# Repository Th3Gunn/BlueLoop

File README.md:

BluePill devboard based project - ultra compact guitar loop switcher controlled entirely through MIDI TRS (something like Morningstar ML5R).
Includes 0.96" I2C LCD module, few buttons (only for programming), USB-C for flashing and USB MIDI. 
5 relay controlled loops (relays controlled with 74HC595 bit shift register), and discrete MOSFET input and  output mute circuit.

Future plans are to make completely custom board (without BluePill module) and to create Windows application for preset programming.

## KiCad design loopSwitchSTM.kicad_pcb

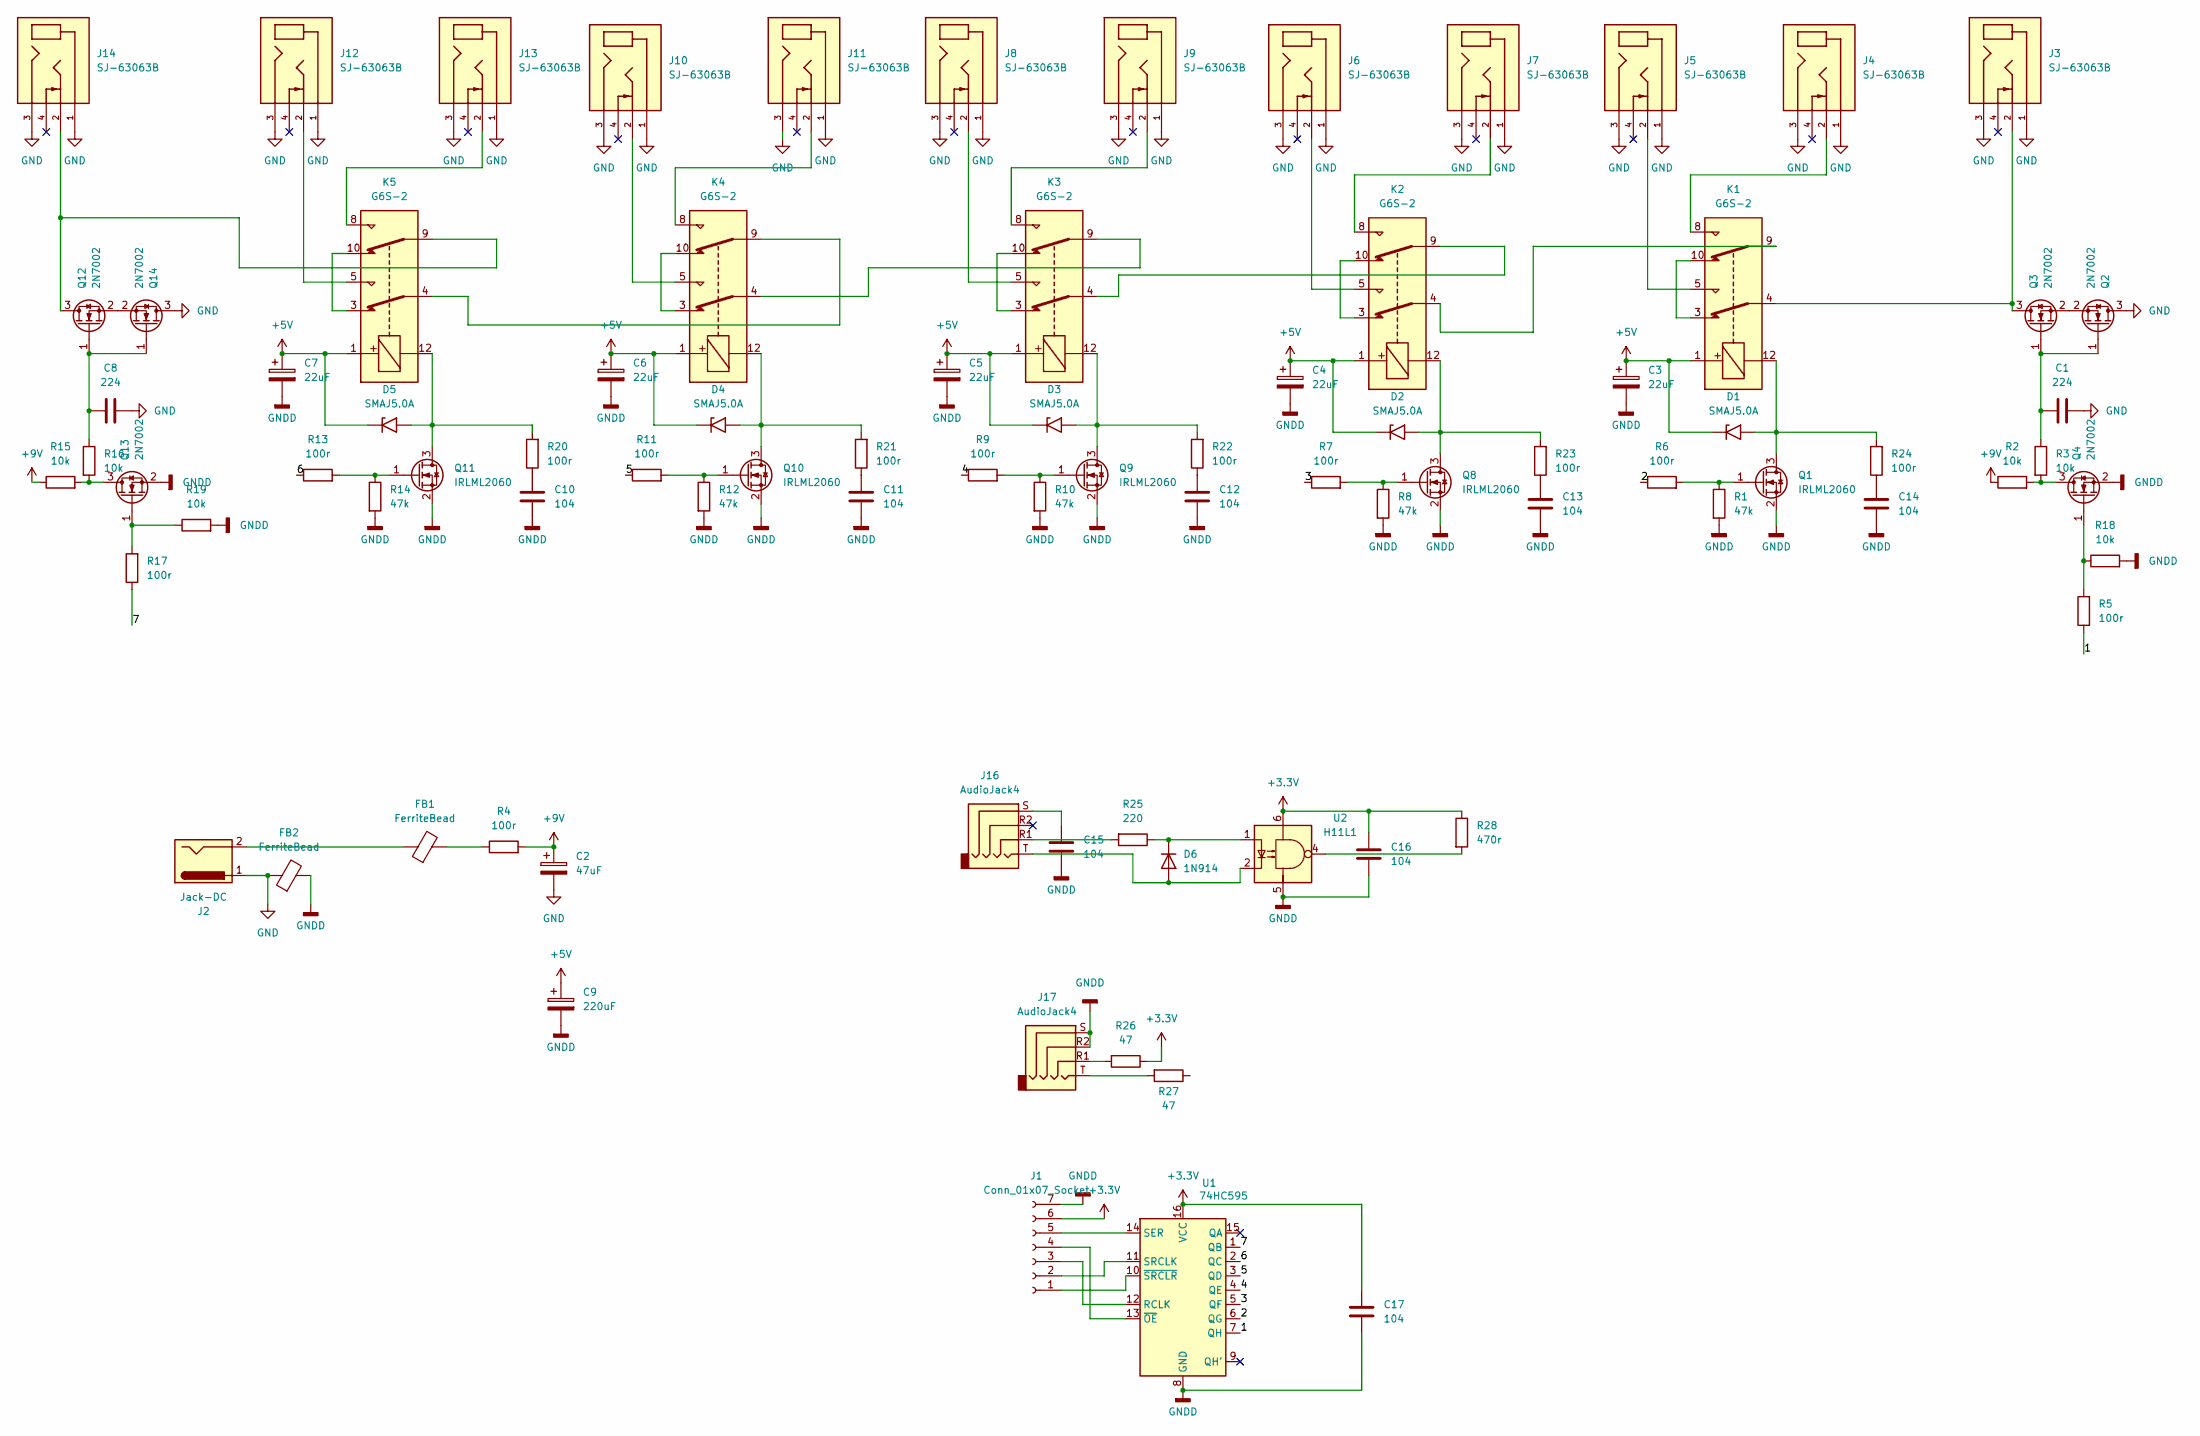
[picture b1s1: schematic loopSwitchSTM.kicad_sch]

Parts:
C1, C8: 224; C_0603_1608Metric_Pad1.08x0.95mm_HandSolder
C2: 47uF; CP_Radial_D5.0mm_P2.50mm
C3, C4, C5, C6, C7: 22uF; CP_Radial_D5.0mm_P2.50mm
C9: 220uF; CP_Radial_D8.0mm_P3.50mm
C10, C11, C12, C13, C14, C15, C16, C17: 104; C_0603_1608Metric_Pad1.08x0.95mm_HandSolder
D1, D2, D3, D4, D5: SMAJ5.0A; D_SMA
D6: 1N914; D_DO-35_SOD27_P7.62mm_Horizontal
FB1, FB2: FerriteBead; L_0805_2012Metric_Pad1.15x1.40mm_HandSolder
J1: Conn_01x07_Socket; PinHeader_1x07_P2.54mm_Vertical
J2: Jack-DC; BarrelJack_GCT_DCJ200-10-A_Horizontal
J3, J4, J5, J6, J7, J8, J9, J10, J11, J12, J13, J14: SJ-63063B; CUI_SJ-63063B; PARTREV 1.0
J16, J17: AudioJack4; PJ-320A
K1, K2, K3, K4, K5: G6S-2; Relay_DPDT_Omron_G6S-2
Q1, Q8, Q9, Q10, Q11: IRLML2060; SOT-23
Q2, Q3, Q4, Q12, Q13, Q14: 2N7002; SOT-23
R1, R8, R10, R12, R14: 47k; R_0603_1608Metric_Pad0.98x0.95mm_HandSolder
R2, R3, R15, R16, R18, R19: 10k; R_0603_1608Metric_Pad0.98x0.95mm_HandSolder
R4, R5, R6, R7, R9, R11, R13, R17, R20, R21, R22, R23, R24: 100r; R_0603_1608Metric_Pad0.98x0.95mm_HandSolder
R25: 220; R_0603_1608Metric_Pad0.98x0.95mm_HandSolder
R26, R27: 47; R_0603_1608Metric_Pad0.98x0.95mm_HandSolder
R28: 470r
U1: 74HC595; SOIC-16W_5.3x10.2mm_P1.27mm
U2: H11L1; DIP-6_W7.62mm_LongPads

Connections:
+3.3V: C16.2, C17.2, J1.6, R26.1, R28.1, U1.16 (VCC), U2.6
+5V: C3.1, C4.1, C5.1, C6.1, C7.1, C9.1, D1.1 (A1), D2.1 (A1), D3.1 (A1), D4.1 (A1), D5.1 (A1), K1.1, K2.1, K3.1, K4.1, K5.1
+9V: C2.1, R2.1, R4.2, R15.1
/1: R5.1, U1.7 (QH)
/2: R6.1, U1.6 (QG)
/3: R7.1, U1.5 (QF)
/4: R9.1, U1.4 (QE)
/5: R11.1, U1.3 (QD)
/6: R13.1, U1.2 (QC)
/7: R17.1, U1.1 (QB)
GND: C1.2, C2.2, C8.2, FB2.1, J2.1, J3.1, J3.3, J4.1, J4.3, J5.1, J5.3, J6.1, J6.3, J7.1, J7.3, J8.1, J8.3, J9.1, J9.3, J10.1, J10.3, J11.1, J11.3, J12.1, J12.3, J13.1, J13.3, J14.1, J14.3, Q2.3 (D), Q14.3 (D)
GNDD: C3.2, C4.2, C5.2, C6.2, C7.2, C9.2, C10.1, C11.1, C12.1, C13.1, C14.1, C15.1, C16.1, C17.1, FB2.2, J1.7, J17.R2, J17.S, Q1.2 (S), Q4.2 (S), Q8.2 (S), Q9.2 (S), Q10.2 (S), Q11.2 (S), Q13.2 (S), R1.2, R8.2, R10.2, R12.2, R14.2, R18.2, R19.2, U1.8 (GND), U2.5
unnamed: C10.2, R20.1
unnamed: C11.2, R21.1
unnamed: C12.2, R22.1
unnamed: C13.2, R23.1
unnamed: C14.2, R24.1
unnamed: C15.2, J16.S
unnamed: D1.2 (A2), K1.12, Q1.3 (D), R24.2
unnamed: D2.2 (A2), K2.12, Q8.3 (D), R23.2
unnamed: D3.2 (A2), K3.12, Q9.3 (D), R22.2
unnamed: D4.2 (A2), K4.12, Q10.3 (D), R21.2
unnamed: D5.2 (A2), K5.12, Q11.3 (D), R20.2
unnamed: D6.2 (A), J16.T, U2.2
unnamed: D6.1 (K), R25.1, U2.1
unnamed: FB1.1, J2.2
unnamed: FB1.2, R4.1
unnamed: J1.1, U1.10 (~SRCLR)
unnamed: J1.2, U1.11 (SRCLK)
unnamed: J1.3, U1.12 (RCLK)
unnamed: J1.4, U1.13 (~OE)
unnamed: J1.5, U1.14 (SER)
unnamed: J4.2, K1.8
unnamed: J5.2, K1.5
unnamed: J6.2, K2.5
unnamed: J7.2, K2.8
unnamed: J8.2, K3.5
unnamed: J9.2, K3.8
unnamed: J10.2, K4.5
unnamed: J11.2, K4.8
unnamed: J12.2, K5.5
unnamed: J13.2, K5.8
unnamed: J16.R1, R25.2
unnamed: J17.R1, R26.2
unnamed: J17.T, R27.2
unnamed: K1.9, K2.4
unnamed: K1.3, K1.10
unnamed: K2.9, K3.4
unnamed: K2.3, K2.10
unnamed: K3.9, K4.4
unnamed: K3.3, K3.10
unnamed: K4.9, K5.4
unnamed: K4.3, K4.10
unnamed: K5.3, K5.10
unnamed: Q1.1 (G), R1.1, R6.2
unnamed: C1.1, Q2.1 (G), Q3.1 (G), R3.1
unnamed: Q2.2 (S), Q3.2 (S)
unnamed: J3.2, K1.4, Q3.3 (D)
unnamed: Q4.3 (D), R2.2, R3.2
unnamed: Q4.1 (G), R5.2, R18.1
unnamed: Q8.1 (G), R7.2, R8.1
unnamed: Q9.1 (G), R9.2, R10.1
unnamed: Q10.1 (G), R11.2, R12.1
unnamed: Q11.1 (G), R13.2, R14.1
unnamed: J14.2, K5.9, Q12.3 (D)
unnamed: C8.1, Q12.1 (G), Q14.1 (G), R16.1
unnamed: Q12.2 (S), Q14.2 (S)
unnamed: Q13.3 (D), R15.2, R16.2
unnamed: Q13.1 (G), R17.2, R19.1
unnamed: R28.2, U2.4

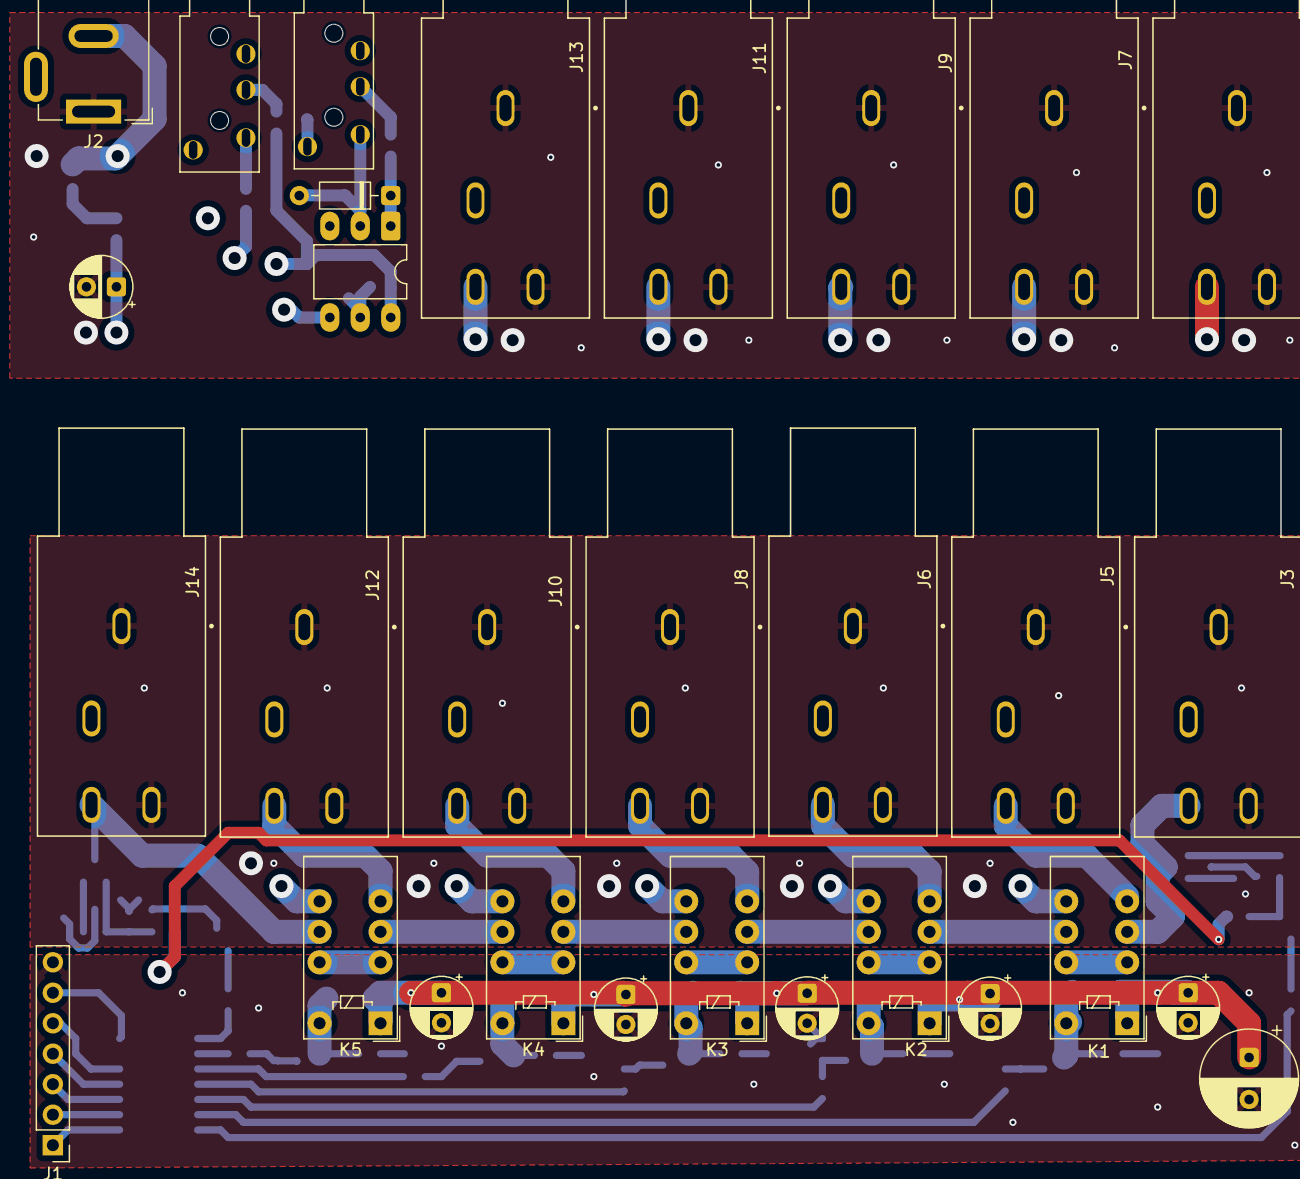
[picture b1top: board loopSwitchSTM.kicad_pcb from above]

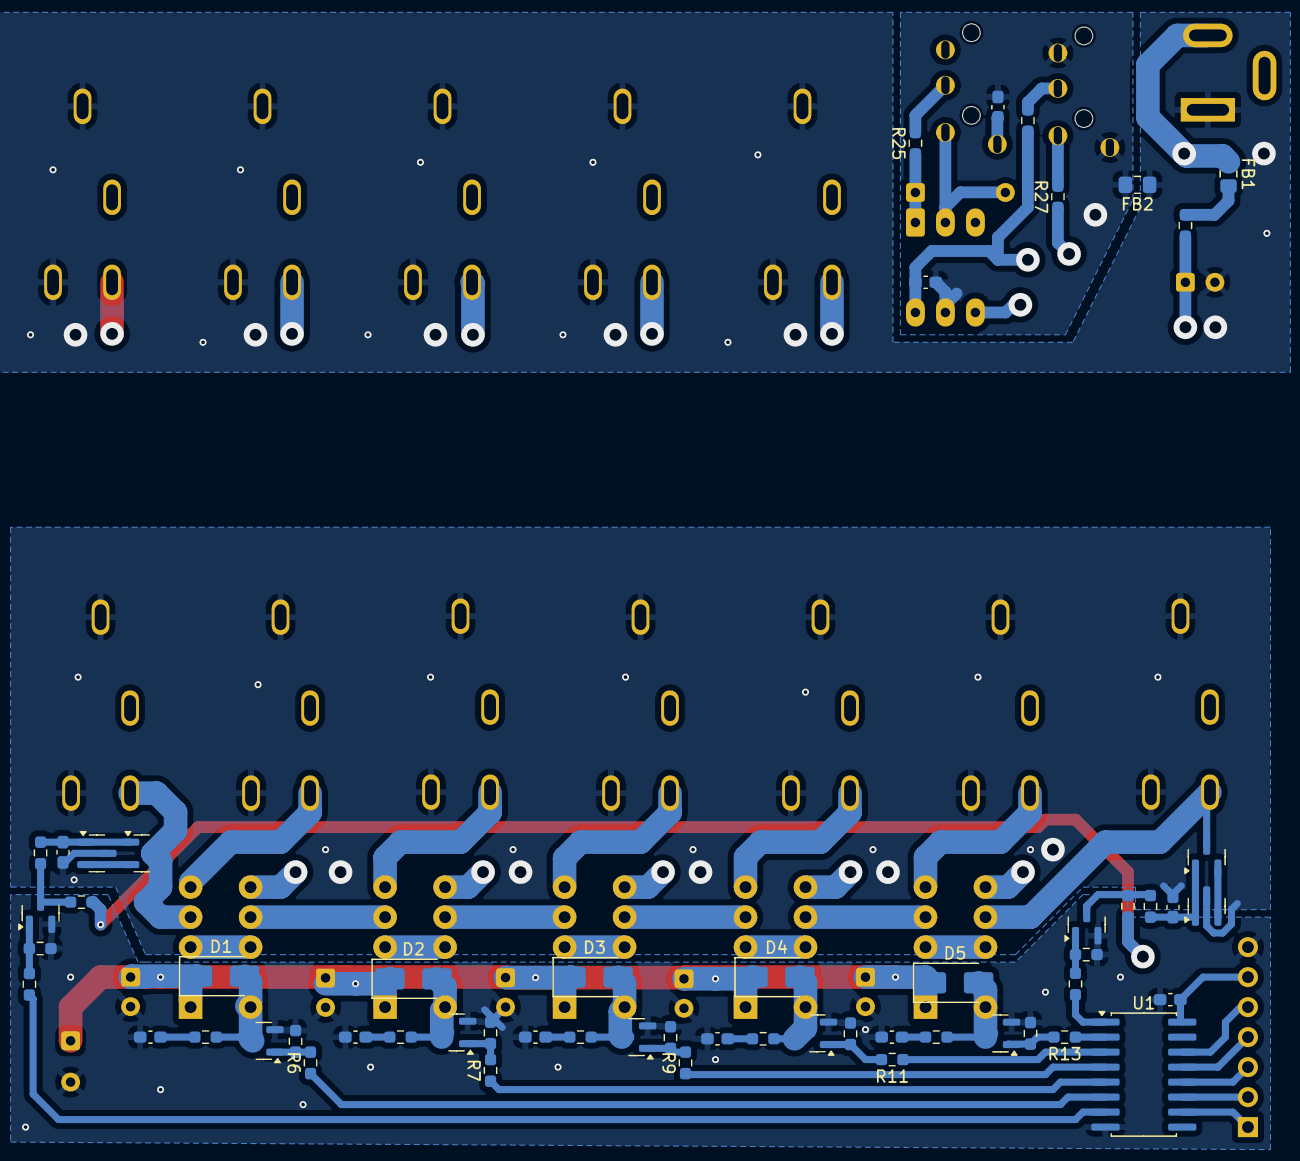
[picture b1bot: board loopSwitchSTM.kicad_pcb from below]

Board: 2 copper layers, 86 parts (56 on the bottom side), 69 nets.

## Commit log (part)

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2026-04-15 added gitignore
2026-05-29 PCB rev 0.1
2026-05-29 Add README content for BluePill project
    Add project description for BluePill guitar loop switcher.
2026-05-29 Update README with future project plans
    Added future plans for custom board and Windows application.
2026-05-29 Update future plans for custom board design
